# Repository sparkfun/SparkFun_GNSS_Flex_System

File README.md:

SparkFun GNSS Flex System
========================================

Our GNSS Flex system is designed to be modular with two board types:

- *Plug-in Modules*

    Each SparkPNT GNSS Flex module features a different GNSS receiver. These boards breakout the various interfaces of a GNSS receiver to the standardized pin configuration for the female headers of the GNSS Flex system. This allows users to easily repair and upgrade their system's GNSS receiver.

- *Carrier Boards*

    These boards host GNSS Flex modules on the standardized male headers of the GNSS Flex system. Their designs usually have a specific intention; such as a breakout board, Raspberry Pi pHAT, SparkPNT product line, etc.

The entire ecosystem is centered around two 2x10-pin, 2mm pitch headers that mate the two types of boards. A standardized pin layout, keeps the ecosystem pin-compatible for upgrades and allows board to be easily swapped for repairs. Depending on the capabilities of the GNSS receiver, these pins will breakout the USB, UART (x4), I<sup>2</sup>C, and SD card interfaces along with any PPS or event signals of the GNSS receiver.

> [!IMPORTANT]
> Depending on the SparkPNT GNSS Flex module, these product will likely require an external antenna:
>
> - Be sure to check out the hookup guide for more information on the GNSS Flex module.
> - Users can also find [GNSS Antennas](https://www.sparkfun.com/gnss/gnss-antennas.html) in our catalog.
>
> Users will have two options for connecting an external GNSS antenna to their GNSS receiver.
>
> - The GNSS Flex modules will usually come with a U.FL connector for an external antenna.
> - For a sturdier connection, a SMA connector on a *carrier board* can utilized. Users can simply jumper the U.FL connectors between the SparkPNT GNSS Flex module and the *carrier board* with a short U.FL cable.

Documentation
--------------

- **[Hookup Guide (mkdocs)](http://docs.sparkfun.com/SparkFun_GNSS_Flex_System/)** - A hookup guide for the entire ecosystem of SparkFun GNSS Flex carrier boards and SparkPNT GNSS Flex modules, hosted by GitHub pages.<br>

Repository Contents
-------------------

- **[/docs](/docs/)** - Online documentation files
  - [/assets](/docs/assets/) - Assets files
    - [/component_documentation](/docs/assets/component_documentation/) - Datasheets for GNSS Flex system's standards
    - [/img/hookup_guide](/docs/assets/img/hookup_guide/) - Images for hookup guide documentation
- [/flex_boards](/flex_boards/)
  - /`<name>` - GNSS Flex board *(or associated GitHub submodule)*
    - /docs - Documentation files for the board
      - /assets - Assets files for the board
        - /3d_model - 3D models for the board
        - /board_files - Design files for the board
          - `kicad_files.zip` - KiCad files for the board
          - `schematic.pdf` - Schematic for the board
          - `dimensions.pdf` - Dimensions for the board
        - /component_documentation - Datasheets for the board
        - /img/hookup_guide - Hookup guide images for the board
    - /hardware - Hardware design files (.brd, .sch)
      - /production - Production files

Product Variants
----------------

- GNSS Modules:
  - GNSS Module *(only)*:
    - [GPS-28138](https://www.sparkfun.com/sparkpnt-gnss-flex-module-mosaic-x5.html) - Septentrio mosaic-X5 GNSS Flex module
    - [GPS-28139](https://www.sparkfun.com/sparkpnt-gnss-flex-module-lg290p.html) - Quectel LG290P GNSS Flex module
    - [GPS-29061](https://www.sparkfun.com/sparkpnt-gnss-flex-module-dan-f10n.html) - u-blox DAN-F10N GNSS Flex module
    - [GPS-29362](https://www.sparkfun.com/sparkpnt-gnss-flex-module-zed-x20p.html) - u-blox ZED-X20P GNSS Flex module
    - [GPS-28870](https://www.sparkfun.com/sparkpnt-gnss-flex-module-lg580p.html) - Quectel LG580P GNSS Flex module
  - GNSS Module w/ IMU:
    - [GPS-29469](https://www.sparkfun.com/sparkpnt-gnss-flex-module-lg290p-im19-imu.html) - Quectel LG290P GNSS Flex module + IM19 IMU
    - [GPS-28997](https://www.sparkfun.com/sparkpnt-gnss-flex-module-zed-x20p-im19-imu.html) - u-blox ZED-X20P GNSS Flex module + IM19 IMU
    - [GPS-29457](https://www.sparkfun.com/sparkpnt-gnss-flex-module-mosaic-x5-im19-imu.html) - Septentrio mosaic-X5 GNSS Flex module + IM19 IMU
- Carrier Boards:
  - [GPS-28137](https://www.sparkfun.com/sparkfun-gnss-flex-phat.html) - GNSS Flex pHAT
  - [GPS-28962](https://www.sparkfun.com/sparkfun-gnss-flex-breakout.html) - GNSS Flex Breakout Board
- Kits:
  - pHAT + GNSS Module *(only)*:
    - [GPS-28766](https://www.sparkfun.com/sparkfun-gnss-flex-phat-mosaic-x5.html) - GNSS Flex pHAT w/ the Septentrio mosaic-X5 GNSS Flex module
    - [GPS-28929](https://www.sparkfun.com/sparkfun-gnss-flex-phat-lg290p.html) - GNSS Flex pHAT w/ the Quectel LG290P GNSS Flex module
    - [GPS-29491](https://www.sparkfun.com/sparkfun-gnss-flex-phat-dan-f10n.html) - GNSS Flex pHAT w/ the u-blox DAN-F10N GNSS Flex module
    - [GPS-29887](https://www.sparkfun.com/sparkfun-gnss-flex-phat-zed-x20p.html) - GNSS Flex pHAT w/ the u-blox ZED-X20P GNSS Flex module
    - [GPS-29890](https://www.sparkfun.com/sparkfun-gnss-flex-phat-lg580p.html) - GNSS Flex pHAT w/ the Quectel LG580P GNSS Flex module
  - pHAT + GNSS Module w/ IMU:
    - [GPS-29891](https://www.sparkfun.com/sparkfun-gnss-flex-phat-lg290p-im19-imu.html) - GNSS Flex pHAT w/ the Quectel LG290P GNSS Flex module + IM19 IMU
    - [GPS-29888](https://www.sparkfun.com/sparkfun-gnss-flex-phat-zed-x20p-im19-imu.html) - GNSS Flex pHAT w/ the u-blox ZED-X20P GNSS Flex module + IM19 IMU
    - [GPS-29889](https://www.sparkfun.com/sparkpnt-gnss-flex-phat-mosaic-x5-im19-imu.html) - GNSS Flex pHAT w/ the Septentrio mosaic-X5 GNSS Flex module + IM19 IMU

Version History
---------------

- [r2025-08](https://github.com/sparkfun/SparkFun_GNSS_Flex_System/releases/tag/r2025-08) - Initial Release
- [r2025-08a](https://github.com/sparkfun/SparkFun_GNSS_Flex_System/releases/tag/r2025-08a) - Docs Update
- [r2025-09](https://github.com/sparkfun/SparkFun_GNSS_Flex_System/releases/tag/r2025-09) - Adds DAN-F10N, ZED-X20P, and LG290P (w/ IMU) GNSS Flex modules
- [r2025-09a](https://github.com/sparkfun/SparkFun_GNSS_Flex_System/releases/tag/r2025-09a) - Adds GNSS Flex Breakout board and Docs Updates
- [r2025-10](https://github.com/sparkfun/SparkFun_GNSS_Flex_System/releases/tag/r2025-10) - Adds LG580P GNSS Flex module and Docs Updates
- [r2025-10a](https://github.com/sparkfun/SparkFun_GNSS_Flex_System/releases/tag/r2025-10a) - Adds mosaic-X5 w/ IMU GNSS Flex module
- [r2025-10b](https://github.com/sparkfun/SparkFun_GNSS_Flex_System/releases/tag/r2025-10b) - Docs Updates and ZED-X20P Firmware Update

> [!NOTE]
>
> The format of the release tag  `r[year]-[month][iteration]`
>
> - **year:** `YYYY` Format
> - **month:** `MM` Format
> - **iteration:** Revisions for that month *(i.e. `none`, `a`, `b`, etc.)*

License Information
-------------------

This product is ***open source***!

Please review the [`LICENSE.md`](./LICENSE.md) file for license information.

If you have any questions or concerns about licensing, please contact technical support on our [SparkFun forums](https://community.sparkfun.com/c/community/general-chit-chat/37).

Distributed as-is; no warranty is given.

- Your friends at SparkFun.

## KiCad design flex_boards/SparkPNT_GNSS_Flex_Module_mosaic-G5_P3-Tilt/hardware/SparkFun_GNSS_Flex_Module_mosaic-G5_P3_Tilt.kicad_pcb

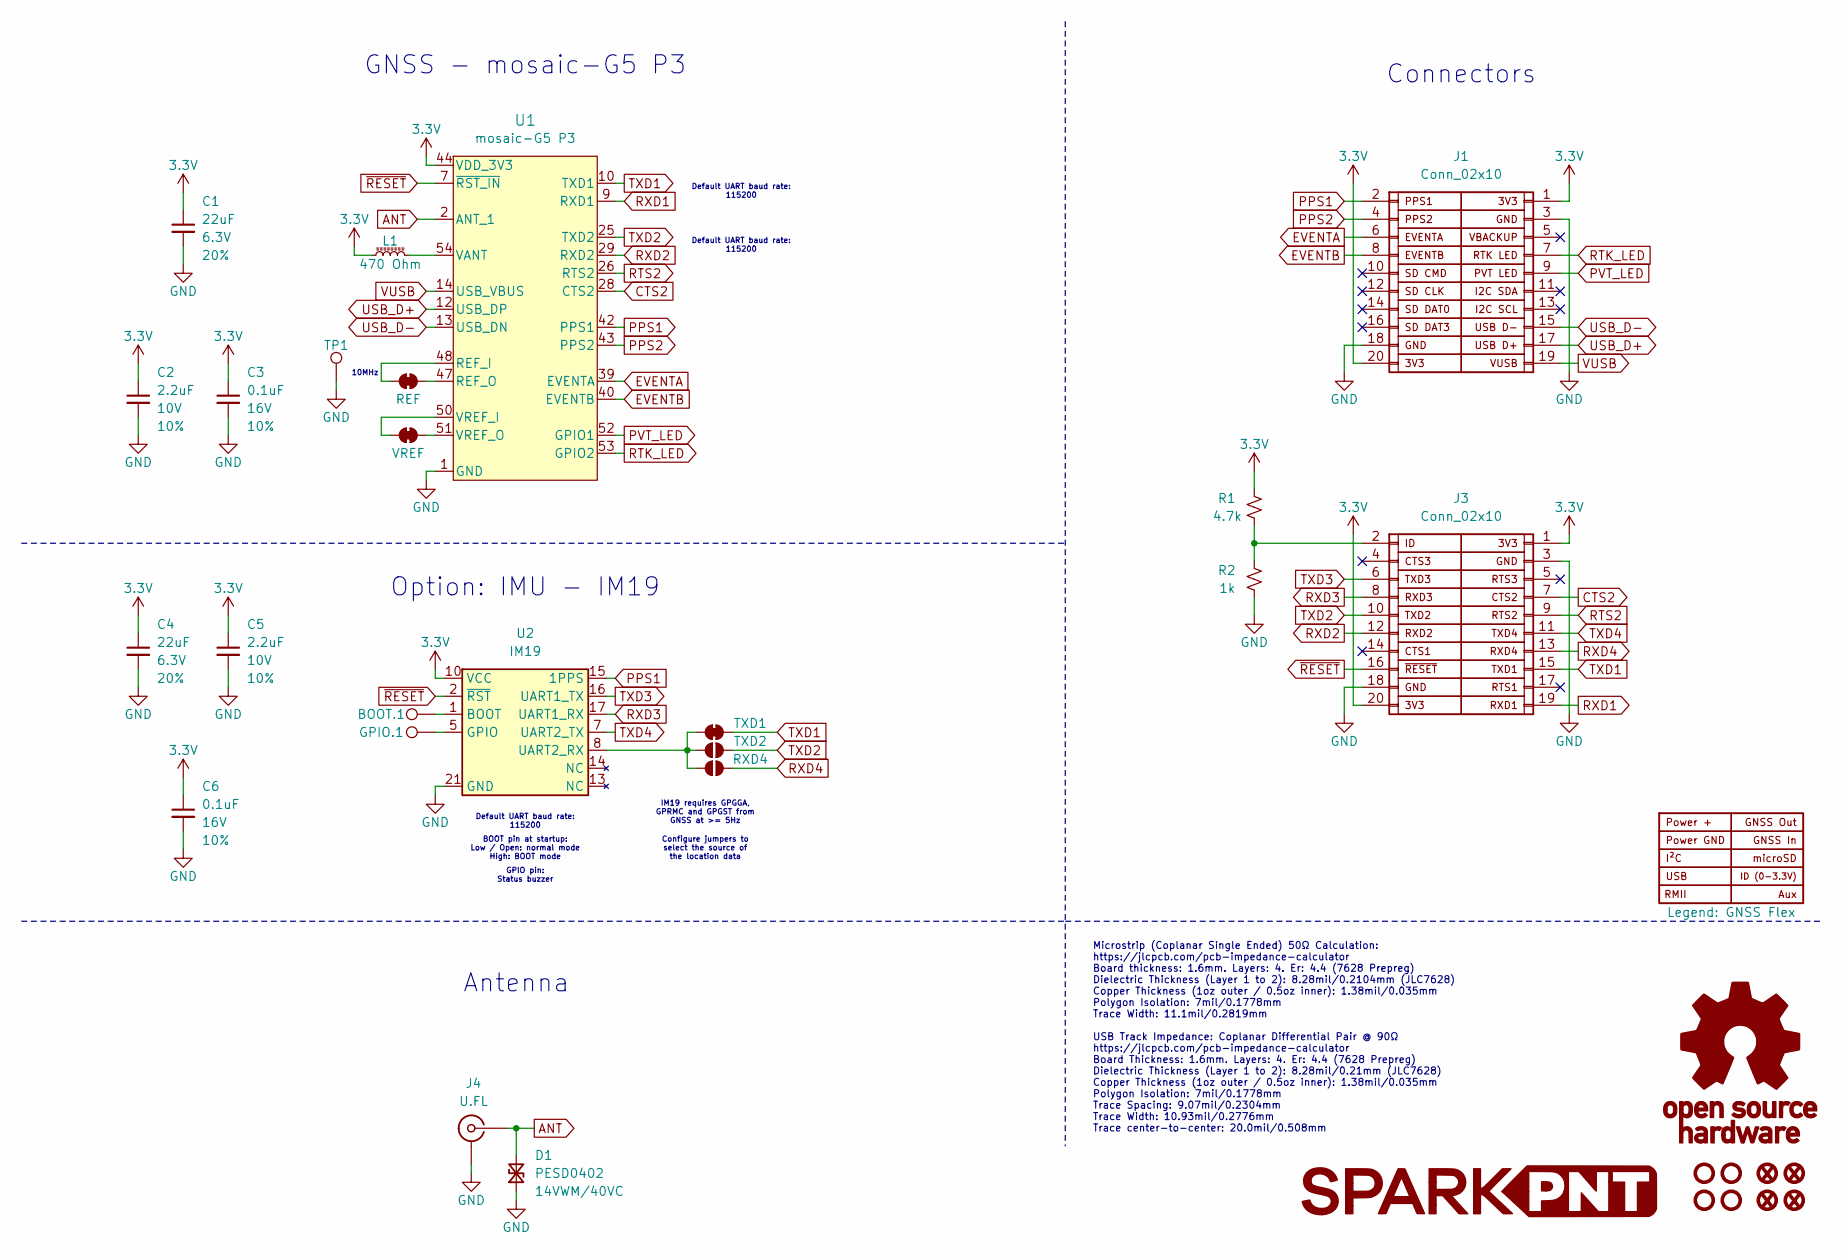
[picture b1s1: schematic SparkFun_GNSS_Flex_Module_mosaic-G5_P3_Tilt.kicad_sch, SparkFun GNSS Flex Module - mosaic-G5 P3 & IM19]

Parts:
BOOT.1: 1.0mm; TestPoint-1.0mm
C1, C4: 22uF; C_0603_1608Metric; Voltage 6.3V; Tolerance 20%
C2, C5: 2.2uF; C_0402_1005Metric; Voltage 10V; Tolerance 10%
C3, C6: 0.1uF; C_0402_1005Metric; Voltage 16V; Tolerance 10%
D1: PESD0402; C_0402_1005Metric; Rating 14VWM/40VC
FID1, FID2, FID3, FID4: Fiducial_0.5mm; Fiducial_0.5mm_Mask1mm
G1: LOGO
G3: OSHW_Logo; Creative_Commons_License
GPIO.1: 1.0mm; TestPoint-1.0mm
J1, J3: Conn_02x10; 2x10_P2.0mm_Socket_Vertical_SMD_Pegs
J2: Legend: GNSS Flex; GNSS_Flex_Template
J4: U.FL
L1: 470 Ohm; C_0603_1608Metric
R1: 4.7k; R_0603_1608Metric
R2: 1k; R_0603_1608Metric
REF.1: REF; Jumper_2_NC_Trace
RXD.4: RXD4; Jumper_2_NO
ST1, ST2, ST3, ST4: Standoff
TP1: 1.25mm; TestPoint-1.25mm
TXD.1: TXD1; Jumper_2_NC_Trace
TXD.2: TXD2; Jumper_2_NO
U1: mosaic-G5 P3; Septentrio_mosaic-G5_LGA54
U2: IM19
VREF.1: VREF; Jumper_2_NC_Trace

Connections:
3.3V: C1.1, C2.1, C3.1, C4.1, C5.1, C6.1, J1.1, J1.20, J3.1, J3.20, L1.1, R1.2, U1.44 (VDD_3V3), U1.45 (VDD_3V3), U2.6 (VCC), U2.10 (VCC)
ANT: D1.2 (A2), J4.1 (In), U1.2 (ANT_1)
CTS2: J3.7, U1.28 (CTS2)
EVENTA: J1.6, U1.39 (EVENTA)
EVENTB: J1.8, U1.40 (EVENTB)
GND: C1.2, C2.2, C3.2, C4.2, C5.2, C6.2, D1.1 (A1), J1.3, J1.18, J3.3, J3.18, J4.2 (Ext), R2.1, TP1.1, U1.1 (GND), U1.3 (GND), U1.4 (GND), U1.6 (GND), U1.11 (GND), U1.17 (GND), U1.21 (GND), U1.27 (GND), U1.34 (GND), U1.41 (GND), U1.46 (GND), U1.49 (GND), U1.55 (GND), U1.56 (GND), U1.57 (GND), U1.58 (GND), U1.59 (GND), U1.60 (GND), U1.61 (GND), U1.62 (GND), U1.63 (GND), U1.64 (GND), U1.65 (GND), U1.66 (GND), U1.67 (GND), U1.68 (GND), U1.69 (GND), U1.70 (GND), U1.71 (GND), U1.72 (GND), U1.73 (GND), U1.74 (GND), U1.75 (GND), U1.76 (GND), U1.77 (GND), U1.78 (GND), U1.79 (GND), U1.80 (GND), U1.81 (GND), U1.82 (GND), U1.83 (GND), U1.84 (GND), U1.85 (GND), U1.86 (GND), U1.87 (GND), U1.88 (GND), U1.89 (GND), U1.90 (GND), U1.91 (GND), U1.92 (GND), U1.93 (GND), U1.94 (GND), U2.3 (GND), U2.4 (GND), U2.9 (GND), U2.18 (GND), U2.21 (GND)
unnamed: J3.2, R1.1, R2.2
unnamed: REF.1.1 (A), U1.47 (REF_O)
unnamed: REF.1.2 (B), U1.48 (REF_I)
unnamed: RXD.4.1 (A), TXD.1.1 (A), TXD.2.1 (A), U2.8 (UART2_RX)
unnamed: L1.2, U1.54 (VANT)
unnamed: U1.50 (VREF_I), VREF.1.2 (B)
unnamed: U1.51 (VREF_O), VREF.1.1 (A)
unnamed: BOOT.1.1, U2.1 (BOOT)
unnamed: GPIO.1.1, U2.5 (GPIO)
PPS1: J1.2, U1.42 (PPS1), U2.15 (1PPS)
PPS2: J1.4, U1.43 (PPS2)
PVT_LED: J1.9, U1.52 (GPIO1)
RTK_LED: J1.7, U1.53 (GPIO2)
RTS2: J3.9, U1.26 (RTS2)
RXD1: J3.19, U1.9 (RXD1)
RXD2: J3.12, U1.29 (RXD2)
RXD3: J3.8, U2.17 (UART1_RX)
RXD4: J3.13, RXD.4.2 (B)
TXD1: J3.15, TXD.1.2 (B), U1.10 (TXD1)
TXD2: J3.10, TXD.2.2 (B), U1.25 (TXD2)
TXD3: J3.6, U2.16 (UART1_TX)
TXD4: J3.11, U2.7 (UART2_TX)
USB_D+: J1.17, U1.12 (USB_DP)
USB_D-: J1.15, U1.13 (USB_DN)
VUSB: J1.19, U1.14 (USB_VBUS)
~RESET: J3.16, U1.7 (~RST_IN), U2.2 (~RST)

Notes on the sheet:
10MHz
Configure jumpers to select the source of the location data
Option: IMU - IM19
IM19 requires GPGGA, GPRMC and GPGST from GNSS at >= 5Hz
Antenna
GPIO pin: Status buzzer
Connectors
Default UART baud rate: 115200
GNSS - mosaic-G5 P3
BOOT pin at startup: Low / Open: normal mode High: BOOT mode
Microstrip (Coplanar Single Ended) 50Ω Calculation: https://jlcpcb.com/pcb-impedance-calculator Board thickness: 1.6mm. Layers: 4. Er: 4.4 (7628 Prepreg) Dielectric Thickness (Layer 1 to 2): 8.28mil/0.2104mm (JLC7628) Copper Thickness (1oz outer / 0.5oz inner): 1.38mil/0.035mm Polygon Isolation: 7m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

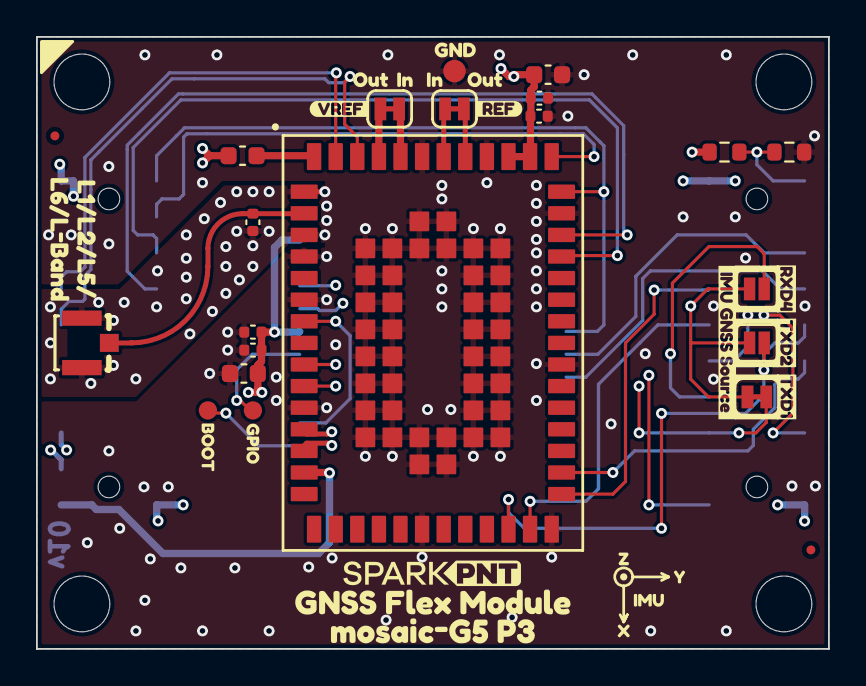
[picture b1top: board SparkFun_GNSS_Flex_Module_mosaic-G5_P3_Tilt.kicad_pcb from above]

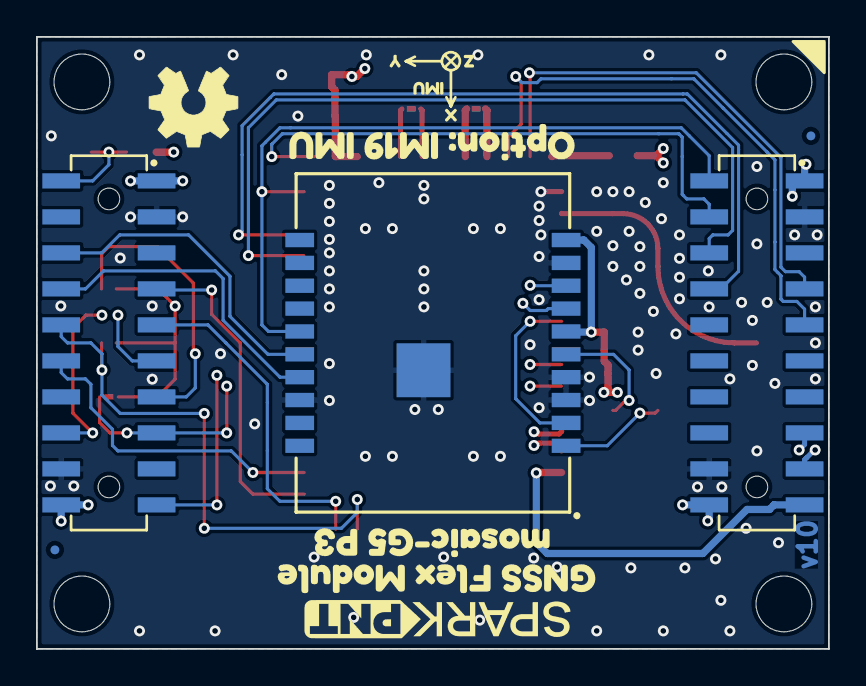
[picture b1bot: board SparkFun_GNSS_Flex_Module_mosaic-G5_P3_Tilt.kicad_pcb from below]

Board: 4 copper layers, 44.0 x 34.0 mm, 62 parts (13 on the bottom side), 32 nets.

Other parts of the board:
Ref**: Val**; OSHW_Logo_5mm
kibuzzard-67E2880B: G***; kibuzzard-67E2880B
kibuzzard-67F7F23B: G***; kibuzzard-67F7F23B
kibuzzard-67F7F255: G***; kibuzzard-67F7F255
kibuzzard-67FE65EC: G***; kibuzzard-67FE65EC
kibuzzard-67FE65FA: G***; kibuzzard-67FE65FA
kibuzzard-67FE650E: G***; kibuzzard-67FE650E
kibuzzard-67FFA928, kibuzzard-67FFA928#2: G***; kibuzzard-67FFA928
kibuzzard-67FFB45E, kibuzzard-67FFB45E#2: G***; kibuzzard-67FFB45E
kibuzzard-67FFB46A, kibuzzard-67FFB46A#2: G***; kibuzzard-67FFB46A
kibuzzard-67FFB450, kibuzzard-67FFB450#2: G***; kibuzzard-67FFB450
kibuzzard-680AACA4, kibuzzard-680AACA4#2: G***; kibuzzard-680AACA4
kibuzzard-680AACC5, kibuzzard-680AACC5#2: G***; kibuzzard-680AACC5
kibuzzard-680AAD48: G***; kibuzzard-680AAD48
kibuzzard-682D7A50: G***; kibuzzard-682D7A50
kibuzzard-682D7B3E: G***; kibuzzard-682D7B3E
kibuzzard-682D7B5F: G***; kibuzzard-682D7B5F
kibuzzard-682D7B21: G***; kibuzzard-682D7B21
kibuzzard-682DBB5B: G***; kibuzzard-682DBB5B
kibuzzard-682DBB98: G***; kibuzzard-682DBB98
kibuzzard-682DBC4E: G***; kibuzzard-682DBC4E
kibuzzard-68068950: G***; kibuzzard-68068950
kibuzzard-68068962: G***; kibuzzard-68068962

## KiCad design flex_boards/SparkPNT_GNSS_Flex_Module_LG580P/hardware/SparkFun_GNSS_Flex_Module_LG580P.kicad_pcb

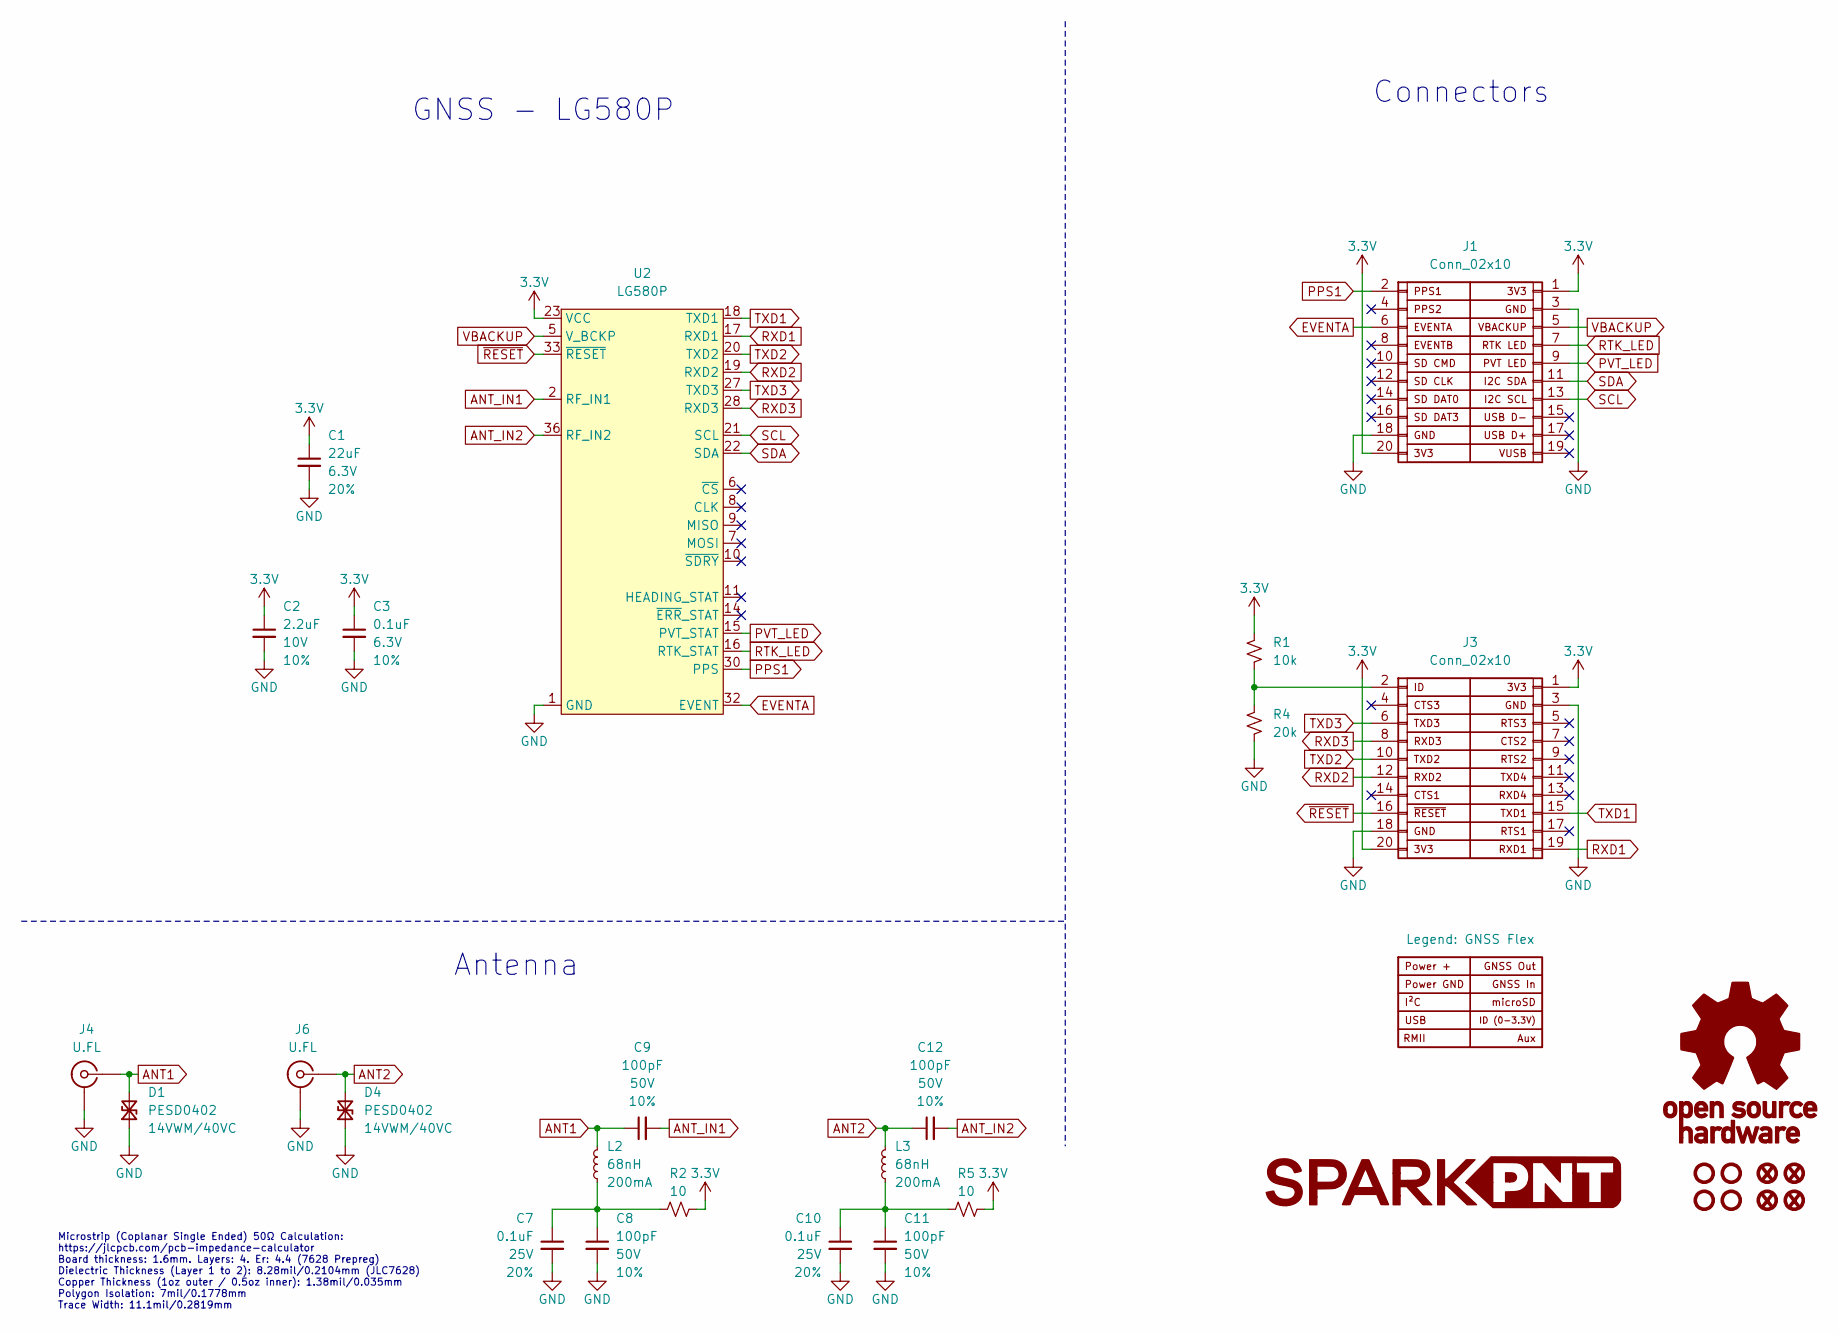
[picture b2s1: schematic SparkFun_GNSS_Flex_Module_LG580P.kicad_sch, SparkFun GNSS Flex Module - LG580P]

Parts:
C1: 22uF; C_0603_1608Metric; Voltage 6.3V; Tolerance 20%
C2: 2.2uF; C_0402_1005Metric; Voltage 10V; Tolerance 10%
C3: 0.1uF; C_0402_1005Metric; Voltage 6.3V; Tolerance 10%
C7, C10: 0.1uF; C_0603_1608Metric; Voltage 25V; Tolerance 20%
C8, C11: 100pF; C_0603_1608Metric; Voltage 50V; Tolerance 10%
C9, C12: 100pF; C_0402_1005Metric; Voltage 50V; Tolerance 10%
D1, D4: PESD0402; C_0402_1005Metric; Rating 14VWM/40VC
FID1, FID2, FID3, FID4: Fiducial_0.5mm; Fiducial_0.5mm_Mask1mm
G1: LOGO
G3: OSHW_Logo; Creative_Commons_License
J1, J3: Conn_02x10; 2x10_2.0mm_Female_Socket_Vertical_SMD_Pegs
J2: Legend: GNSS Flex; GNSS_Flex_Template
J4, J6: U.FL
L2, L3: 68nH; C_0402_1005Metric
R1: 10k; R_0603_1608Metric
R2, R5: 10; R_0603_1608Metric
R4: 20k; R_0603_1608Metric
ST1, ST2, ST3, ST4: Standoff
U2: LG580P; Quectel_LG580P

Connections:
3.3V: C1.1, C2.1, C3.1, J1.1, J1.20, J3.1, J3.20, R1.2, R2.2, R5.2, U2.23 (VCC), U2.24 (VCC)
ANT1: C9.1, D1.2 (A2), J4.1 (In), L2.2
ANT2: C12.1, D4.2 (A2), J6.1 (In), L3.2
ANT_IN1: C9.2, U2.2 (RF_IN1)
ANT_IN2: C12.2, U2.36 (RF_IN2)
EVENTA: J1.6, U2.32 (EVENT)
GND: C1.2, C2.2, C3.2, C7.2, C8.2, C10.2, C11.2, D1.1 (A1), D4.1 (A1), J1.3, J1.18, J3.3, J3.18, J4.2 (Ext), J6.2 (Ext), R4.1, U2.1 (GND), U2.3 (GND), U2.4 (GND), U2.34 (GND), U2.35 (GND), U2.37 (GND), U2.41 (GND), U2.43 (GND), U2.45 (GND), U2.49 (GND)
unnamed: C7.1, C8.1, L2.1, R2.1
unnamed: C10.1, C11.1, L3.1, R5.1
unnamed: J3.2, R1.1, R4.2
PPS1: J1.2, U2.30 (PPS)
PVT_LED: J1.9, U2.15 (PVT_STAT)
RTK_LED: J1.7, U2.16 (RTK_STAT)
RXD1: J3.19, U2.17 (RXD1)
RXD2: J3.12, U2.19 (RXD2)
RXD3: J3.8, U2.28 (RXD3)
SCL: J1.13, U2.21 (SCL)
SDA: J1.11, U2.22 (SDA)
TXD1: J3.15, U2.18 (TXD1)
TXD2: J3.10, U2.20 (TXD2)
TXD3: J3.6, U2.27 (TXD3)
VBACKUP: J1.5, U2.5 (V_BCKP)
~RESET: J3.16, U2.33 (~RESET)

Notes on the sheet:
Antenna
Connectors
GNSS - LG580P
Microstrip (Coplanar Single Ended) 50Ω Calculation: https://jlcpcb.com/pcb-impedance-calculator Board thickness: 1.6mm. Layers: 4. Er: 4.4 (7628 Prepreg) Dielectric Thickness (Layer 1 to 2): 8.28mil/0.2104mm (JLC7628) Copper Thickness (1oz outer / 0.5oz inner): 1.38mil/0.035mm Polygon Isolation: 7m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

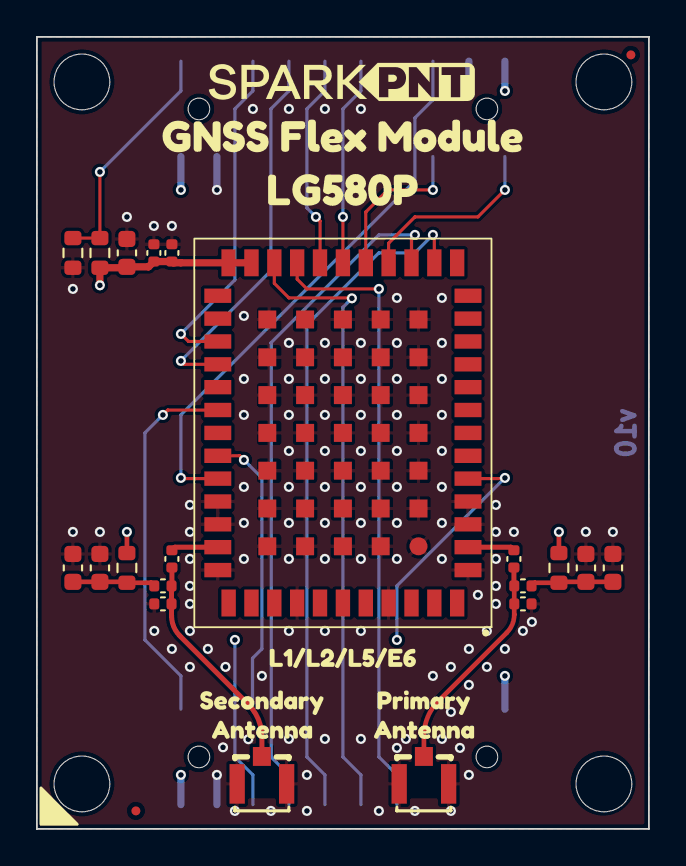
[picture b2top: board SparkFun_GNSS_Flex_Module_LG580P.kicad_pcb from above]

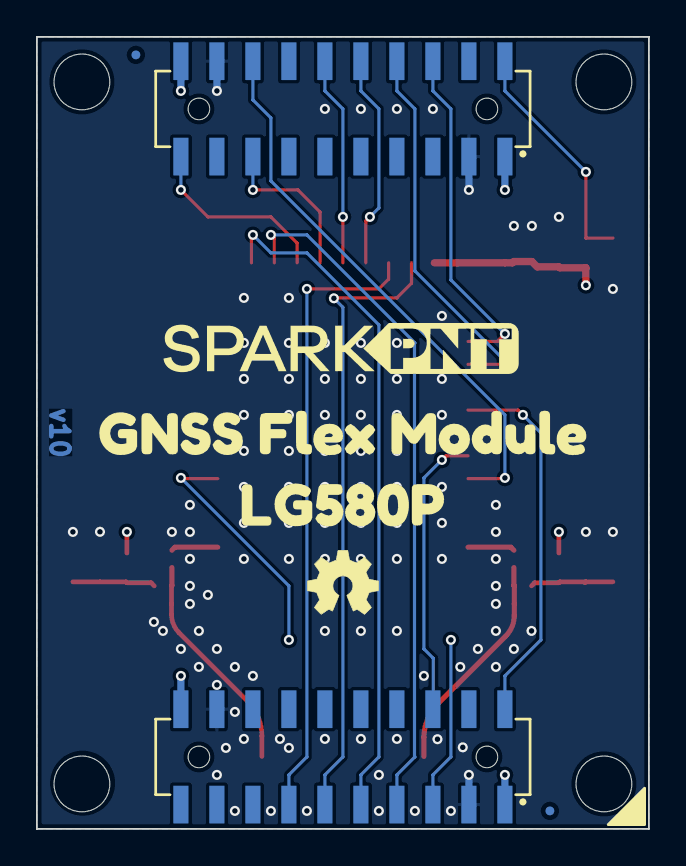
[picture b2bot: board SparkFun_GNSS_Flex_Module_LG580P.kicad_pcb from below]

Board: 4 copper layers, 34.0 x 44.0 mm, 42 parts (8 on the bottom side), 23 nets.

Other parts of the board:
Ref**: Val**; OSHW_Logo_4mm
kibuzzard-67DC4CF4: G***; kibuzzard-67DC4CF4
kibuzzard-67DC4D0C: G***; kibuzzard-67DC4D0C
kibuzzard-67EC9ED9: G***; kibuzzard-67EC9ED9
kibuzzard-67EC9EE7: G***; kibuzzard-67EC9EE7
kibuzzard-67ECA530: G***; kibuzzard-67ECA530
kibuzzard-67ECA543: G***; kibuzzard-67ECA543
kibuzzard-67975357: G***; kibuzzard-67975357
kibuzzard-67975369, kibuzzard-67975369#2: G***; kibuzzard-67975369

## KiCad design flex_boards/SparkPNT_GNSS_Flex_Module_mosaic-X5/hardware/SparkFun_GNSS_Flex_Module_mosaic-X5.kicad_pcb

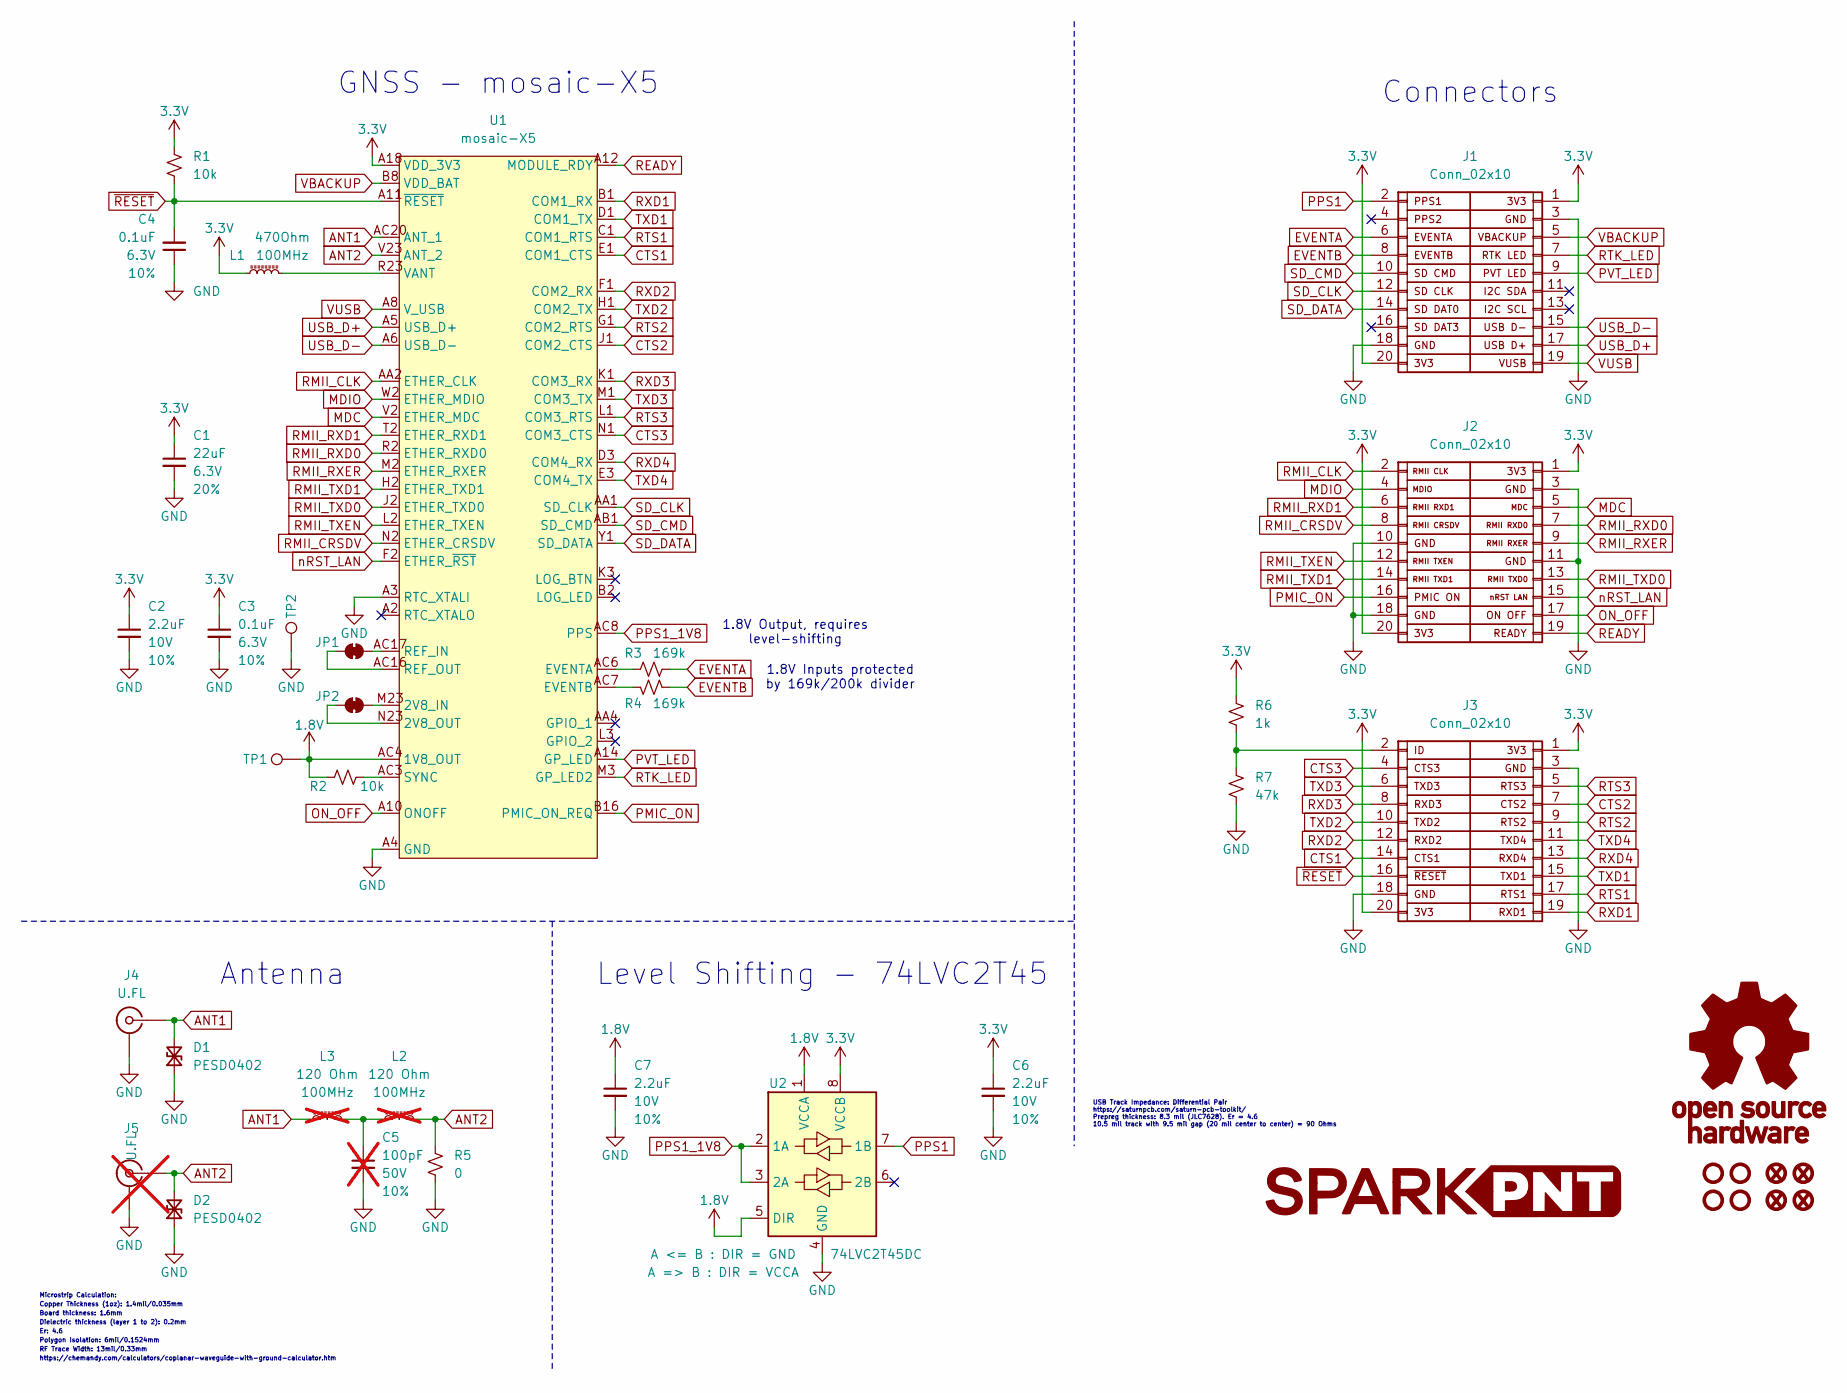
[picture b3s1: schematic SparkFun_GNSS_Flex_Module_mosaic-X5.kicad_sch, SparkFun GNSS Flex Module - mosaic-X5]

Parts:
C1: 22uF; C_0603_1608Metric; Voltage 6.3V; Tolerance 20%
C2, C6, C7: 2.2uF; C_0402_1005Metric; Voltage 10V; Tolerance 10%
C3, C4: 0.1uF; C_0402_1005Metric; Voltage 6.3V; Tolerance 10%
C5: 100pF; C_0402_1005Metric; Voltage 50V; Tolerance 10%; not fitted
D1, D2: PESD0402; C_0402_1005Metric
FID1, FID2, FID3, FID4: Fiducial_0.5mm; Fiducial_0.5mm_Mask1mm
G1: LOGO
G3: OSHW_Logo; Creative_Commons_License
J1, J2, J3: Conn_02x10; 2x10_2.0mm_Female_Socket_Vertical_SMD_Pegs
J4: U.FL
J5: U.FL; not fitted
JP1, JP2: Jumper_2_NC_Trace
L1: 470Ohm; C_0603_1608Metric
L2, L3: 120 Ohm; C_0402_1005Metric; not fitted
R1, R2: 10k; R_0402_1005Metric
R3, R4: 169k; R_0603_1608Metric
R5: 0; R_0402_1005Metric
R6: 1k; R_0603_1608Metric
R7: 47k; R_0603_1608Metric
ST1, ST2, ST3, ST4: Standoff
TP1, TP2: 1.0mm; TestPoint-1.0mm
U1: mosaic-X5; MOSAIC_LGA
U2: 74LVC2T45DC; VSSOP8_SOT765-1

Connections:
1.8V: C7.1, R2.1, TP1.1, U1.AC4 (1V8_OUT), U2.1 (VCCA), U2.5 (DIR)
3.3V: C1.1, C2.1, C3.1, C6.1, J1.1, J1.20, J2.1, J2.20, J3.1, J3.20, L1.1, R1.2, R6.1, U1.A18 (VDD_3V3), U1.A19 (VDD_3V3), U1.A20 (VDD_3V3), U1.B18 (VDD_3V3), U1.B19 (VDD_3V3), U1.B20 (VDD_3V3), U1.C18 (VDD_3V3), U1.C19 (VDD_3V3), U1.C20 (VDD_3V3), U2.8 (VCCB)
ANT1: D1.2 (A2), J4.1 (In), L3.2, U1.AC20 (ANT_1)
ANT2: D2.2 (A2), J5.1 (In), L2.1, R5.2, U1.V23 (ANT_2)
CTS1: J3.14, U1.E1 (COM1_CTS)
CTS2: J3.7, U1.J1 (COM2_CTS)
CTS3: J3.4, U1.N1 (COM3_CTS)
EVENTA: J1.6, R3.2
EVENTB: J1.8, R4.2
GND: C1.2, C2.2, C3.2, C4.1, C5.2, C6.2, C7.2, D1.1 (A1), D2.1 (A1), J1.3, J1.18, J2.3, J2.10, J2.11, J2.18, J3.3, J3.18, J4.2 (Ext), J5.2 (Ext), R5.1, R7.1, TP2.1, U1.A3 (RTC_XTALI), U1.A4 (GND), U1.A7 (GND), U1.A15 (GND), U1.A16 (GND), U1.A17 (GND), U1.A21 (GND), U1.A22 (GND), U1.A23 (GND), U1.AA13 (GND), U1.AA14 (GND), U1.AA15 (GND), U1.AA16 (GND), U1.AA17 (GND), U1.AA18 (GND), U1.AA19 (GND), U1.AA20 (GND), U1.AA21 (GND), U1.AA22 (GND), U1.AA23 (GND), U1.AB2 (GND), U1.AB3 (GND), U1.AB4 (GND), U1.AB5 (GND), U1.AB6 (GND), U1.AB7 (GND), U1.AB8 (GND), U1.AB13 (GND), U1.AB14 (GND), U1.AB15 (GND), U1.AB16 (GND), U1.AB17 (GND), U1.AB18 (GND), U1.AB19 (GND), U1.AB20 (GND), U1.AB21 (GND), U1.AB22 (GND), U1.AB23 (GND), U1.AC13 (GND), U1.AC15 (GND), U1.AC18 (GND), U1.AC19 (GND), U1.AC21 (GND), U1.AC22 (GND), U1.AC23 (GND), U1.B4 (GND), U1.B5 (GND), U1.B6 (GND), U1.B7 (GND), U1.B13 (GND), U1.B17 (GND), U1.B21 (GND), U1.C4 (GND), U1.C7 (GND), U1.C15 (GND), U1.C16 (GND), U1.C17 (GND), U1.C23 (GND), U1.D2 (GND), U1.D21 (GND), U1.D22 (GND), U1.D23 (GND), U1.E2 (GND), U1.E21 (GND), U1.E22 (GND), U1.E23 (GND), U1.F21 (GND), U1.F22 (GND), U1.F23 (GND), U1.G2 (GND), U1.G21 (GND), U1.G23 (GND), U1.H21 (GND), U1.H22 (GND), U1.H23 (GND), U1.J21 (GND), U1.J22 (GND), U1.J23 (GND), U1.K2 (GND), U1.K21 (GND), U1.K22 (GND), U1.K23 (GND), U1.L21 (GND), U1.L22 (GND), U1.L23 (GND), U1.M21 (GND), U1.M22 (GND), U1.N21 (GND), U1.N22 (GND), U1.P1 (GND), U1.P2 (GND), U1.P3 (GND), U1.P21 (GND), U1.P22 (GND), U1.R3 (GND), U1.R21 (GND), U1.R22 (GND), U1.T21 (GND), U1.T22 (GND), U1.T23 (GND), U1.U2 (GND), U1.U21 (GND), U1.U22 (GND), U1.U23 (GND), U1.V21 (GND), U1.V22 (GND), U1.W21 (GND), U1.W22 (GND), U1.W23 (GND), U1.Y2 (GND), U1.Y21 (GND), U1.Y22 (GND), U1.Y23 (GND), U2.4 (GND)
MDC: J2.5, U1.V2 (ETHER_MDC)
MDIO: J2.4, U1.W2 (ETHER_MDIO)
unnamed: C5.1, L2.2, L3.1
unnamed: J3.2, R6.2, R7.2
unnamed: JP1.1 (A), U1.AC16 (REF_OUT)
unnamed: JP1.2 (B), U1.AC17 (REF_IN)
unnamed: JP2.1 (A), U1.N23 (2V8_OUT)
unnamed: JP2.2 (B), U1.M23 (2V8_IN)
unnamed: R3.1, U1.AC6 (EVENTA)
unnamed: R4.1, U1.AC7 (EVENTB)
unnamed: R2.2, U1.AC3 (SYNC)
ON_OFF: J2.17, U1.A10 (ONOFF)
PMIC_ON: J2.16, U1.B16 (PMIC_ON_REQ)
PPS1: J1.2, U2.7 (1B)
PPS1_1V8: U1.AC8 (PPS), U2.2 (1A), U2.3 (2A)
PVT_LED: J1.9, U1.A14 (GP_LED)
READY: J2.19, U1.A12 (MODULE_RDY)
RMII_CLK: J2.2, U1.AA2 (ETHER_CLK)
RMII_CRSDV: J2.8, U1.N2 (ETHER_CRSDV)
RMII_RXD0: J2.7, U1.R2 (ETHER_RXD0)
RMII_RXD1: J2.6, U1.T2 (ETHER_RXD1)
RMII_RXER: J2.9, U1.M2 (ETHER_RXER)
RMII_TXD0: J2.13, U1.J2 (ETHER_TXD0)
RMII_TXD1: J2.14, U1.H2 (ETHER_TXD1)
RMII_TXEN: J2.12, U1.L2 (ETHER_TXEN)
RTK_LED: J1.7, U1.M3 (GP_LED2)
RTS1: J3.17, U1.C1 (COM1_RTS)
RTS2: J3.9, U1.G1 (COM2_RTS)
RTS3: J3.5, U1.L1 (COM3_RTS)
RXD1: J3.19, U1.B1 (COM1_RX)
RXD2: J3.12, U1.F1 (COM2_RX)
RXD3: J3.8, U1.K1 (COM3_RX)
RXD4: J3.13, U1.D3 (COM4_RX)
SD_CLK: J1.12, U1.AA1 (SD_CLK)
SD_CMD: J1.10, U1.AB1 (SD_CMD)
SD_DATA: J1.14, U1.Y1 (SD_DATA)
TXD1: J3.15, U1.D1 (COM1_TX)
TXD2: J3.10, U1.H1 (COM2_TX)
TXD3: J3.6, U1.M1 (COM3_TX)
TXD4: J3.11, U1.E3 (COM4_TX)
USB_D+: J1.17, U1.A5 (USB_D+)
USB_D-: J1.15, U1.A6 (USB_D-)
VANT: L1.2, U1.P23 (VANT), U1.R23 (VANT)
VBACKUP: J1.5, U1.B8 (VDD_BAT)
VUSB: J1.19, U1.A8 (V_USB)
nRST_LAN: J2.15, U1.F2 (ETHER_~RST)
~RESET: C4.2, J3.16, R1.1, U1.A11 (~RESET)

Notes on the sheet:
Copper Thickness (1oz): 1.4mil/0.035mm
Board thickness: 1.6mm
Er: 4.6
Antenna
Dielectric thickness (layer 1 to 2): 0.2mm
https://chemandy.com/calculators/coplanar-waveguide-with-ground-calculator.htm
USB Track Impedance: Differential Pair https://saturnpcb.com/saturn-pcb-toolkit/ Prepreg thickness: 8.3 mil (JLC7628). Er = 4.6 10.5 mil track with 9.5 mil gap (20 mil center to center) = 90 Ohms
RF Trace Width: 13mil/0.33mm
1.8V Output, requires level-shifting
Connectors
GNSS - mosaic-X5
Microstrip Calculation:
1.8V Inputs protected by 169k/200k divider
Polygon Isolation: 6mil/0.1524mm
Level Shifting - 74LVC2T45

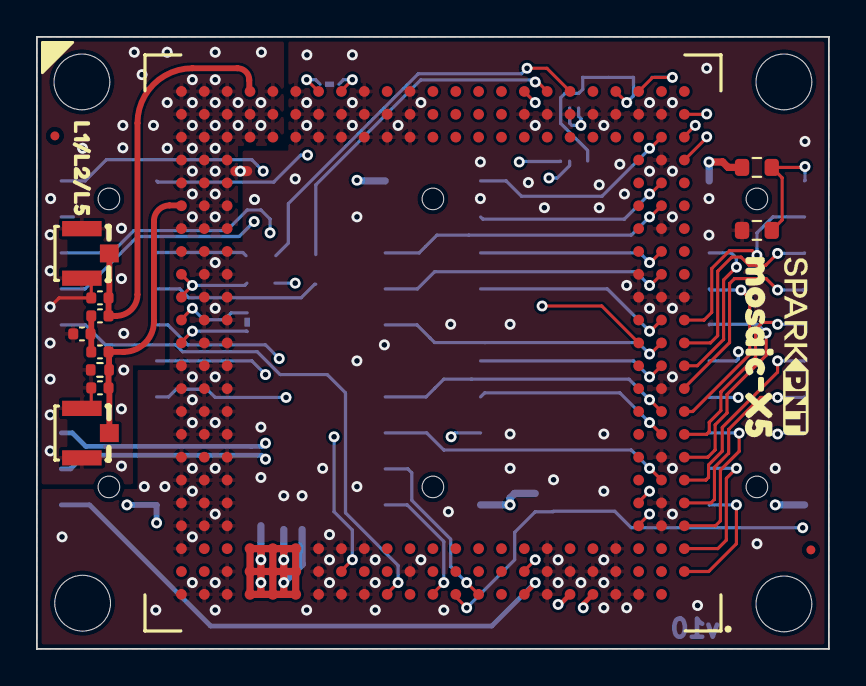
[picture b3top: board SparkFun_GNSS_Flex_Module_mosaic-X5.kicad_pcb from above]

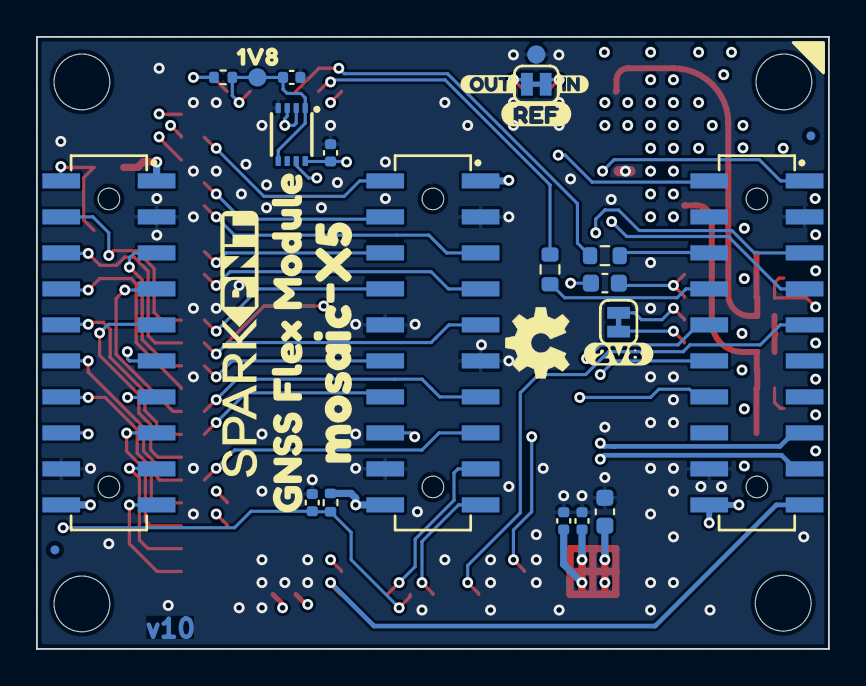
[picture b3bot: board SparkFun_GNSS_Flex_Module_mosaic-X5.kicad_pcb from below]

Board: 4 copper layers, 44.0 x 34.0 mm, 49 parts (29 on the bottom side), 57 nets.

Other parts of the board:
Ref**: Val**; OSHW_Logo_4mm
kibuzzard-67DC454B: G***; kibuzzard-67DC454B
kibuzzard-67DC4556: G***; kibuzzard-67DC4556
kibuzzard-67DC4600: G***; kibuzzard-67DC4600
kibuzzard-679B2C5E: G***; kibuzzard-679B2C5E
kibuzzard-679B2C8E: G***; kibuzzard-679B2C8E
kibuzzard-679B4D6E: G***; kibuzzard-679B4D6E
kibuzzard-679B4D74: G***; kibuzzard-679B4D74
kibuzzard-6790B939: G***; kibuzzard-6790B939
kibuzzard-6790BA7F: G***; kibuzzard-6790BA7F

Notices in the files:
parts and their libraries:
https://creativecommons.org/licenses/by-sa/4.0
Released under the Creative Commons Attribution Share-Alike 4.0 License
